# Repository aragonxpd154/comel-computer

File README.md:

<p align="center">
  <b>Um Commodore 64 de verdade — BASIC V2, tela de 7" VGA, 2 portas USB para teclado e joystick — ligado à rede por uma TSDA 4011R1.</b><br>
  Uma placa única em KiCad (esquemático, PCB roteada, arquivos de fábrica, 3D com componentes reais),<br>
  a engenharia reversa da TSDA e uma carcaça compacta com a tela inclinada, pronta para cortar a laser.
</p>

<p align="center">
  
</p>

---

## Sumário

- [Visão geral](#visão-geral)
- [Arquitetura](#arquitetura)
- [Placa COMEL](#placa-comel--o-commodore-e-a-energia-numa-placa-só)
- [Carcaça cortada a laser](#carcaça-cortada-a-laser)
- [TSDA 4011R1 — a placa de rede](#tsda-4011r1--a-placa-de-rede)
- [Lista de materiais](#lista-de-materiais)
- [Guia passo a passo](#guia-passo-a-passo)
- [Estrutura do repositório](#estrutura-do-repositório)
- [Limitações e pontos a confirmar](#limitações-e-pontos-a-confirmar)
- [Referências](#referências) · [Licença](#licença)

---

## Visão geral

A **TSDA 4011R1** é a placa de comunicação da remota FLEX TSDA usada na transmissão: um Digi Connect ME que coloca uma
porta serial na rede. Este projeto aproveita essa placa como "modem" de um **Commodore 64 recriado num Raspberry Pi
Pico 2**: o Pico emula o C64 (6502, VIC-II, SID, KERNAL e BASIC V2), mostra a imagem numa tela de 7" VGA e fala com a
TSDA pela serial. Um Telnet no IP da TSDA conversa com o programa BASIC, como uma BBS dos anos 80.

| | Conteúdo | Onde |
|---|---|---|
| 🟦 | **Placa COMEL** — Pico 2, VGA RGB332, 2 × USB host (teclado), microSD, áudio (SID), joystick, serial até a TSDA **e** a entrada da Mean Well RD-35A (5 V / 12 V) com TVS, polyfuse e LED por trilho. 132 × 64 mm, **DRC 0** | [`hardware/comel`](hardware/comel) |
| 🏭 | Gerbers X2, furação, BOM, pick-and-place, STEP, PDFs de esquemático e montagem | [`hardware/comel/fab`](hardware/comel/fab) |
| 📦 | Carcaça compacta (230 × 128 × 190 mm) com a tela de 7" inclinada 25°, chapa de 3 mm: 2 chapas de 600 × 400 mm em **SVG e DXF**, gerada a partir do layout da placa | [`case`](case) |
| 🔍 | Engenharia reversa da TSDA 4011R1, com modelo 3D reconstruído das fotos | [`docs/tsda-4011r1.md`](docs/tsda-4011r1.md) |
| 🧊 | Modelos 3D (STEP/GLB/STL) e visualizador three.js com a montagem completa | [`docs/3d`](docs/3d) |
| 💾 | **Firmware do C64** pronto para gravar ([`comel.uf2`](firmware/bin/comel.uf2)): 6510/VIC-II/CIAs/SID, VGA 640×480 em PIO, 2 × USB host para teclado, áudio PWM, LOAD/SAVE no microSD | [`firmware`](firmware) |
| 🔁 | Pipeline reprodutível: um arquivo Python descreve os circuitos; o resto é gerado | [`tools/eda/designs.py`](tools/eda/designs.py) |

---

## Arquitetura

```mermaid
flowchart LR
  AC["Tomada<br/>módulo IEC + fusível"] --> PSU["Mean Well RD-35A<br/>5 V / 4 A · 12 V / 1 A"]
  PSU -- "J10" --> PWR
  PWR -- "5 V · J11" --> TSDA
  PWR -- "12 V · J12" --> LCD
  subgraph COMEL["Placa COMEL"]
    direction TB
    PWR["Entrada da fonte<br/>TVS · polyfuse · LEDs"]
    PICO(("Pico 2<br/>emulador C64"))
    VGA["DAC RGB332"]
    KB["2 × USB-A<br/>host em PIO"]
    SD["microSD"]
    AUD["Áudio SID<br/>RC 2 polos"]
    JOY["Joystick DB9"]
    SER["Serial<br/>TTL / MAX3232"]
    PWR -- "5 V" --> PICO
  end
  PICO --> VGA -- "IDC 2×5" --> LCD["Tela de 7 pol. 800×480<br/>PCB800099"]
  KB --- PICO
  SD --- PICO
  PICO --> AUD
  JOY --> PICO
  PICO --- SER -- "UART" --> TSDA["TSDA 4011R1<br/>Digi Connect ME"]
  TSDA -- "Ethernet<br/>Telnet / HTTP" --> NET(("Rede"))
```

---

## Placa COMEL — o Commodore e a energia numa placa só

<table>
<tr>
<td width="50%"></td>
<td width="50%"></td>
</tr>
<tr><td align="center"><sub>Face superior, renderizada a partir dos Gerbers</sub></td><td align="center"><sub>Modelo 3D com os modelos STEP dos componentes</sub></td></tr>
</table>

<p align="center"><sub>Esquemático em blocos funcionais (folha A2) — <a href="docs/images/comel-schematic.svg">SVG vetorial</a> · <a href="hardware/comel/fab/comel-schematic.pdf">PDF</a></sub></p>

A revisão anterior tinha duas placas (MAIN e PWR). Agora tudo cabe em **132 × 64 mm**: o lado esquerdo é o Commodore,
o lado direito é a entrada da fonte. Só a Mean Well RD-35A fica fora da placa.

| Bloco | Componentes | Como funciona |
|---|---|---|
| Processador | U1 Pico 2 em 2 barras fêmea | RP2350 roda o emulador do C64; o USB sai pela lateral da carcaça para gravar o firmware |
| Vídeo | R1–R10, J1 | DAC de resistores RGB332 (256 cores): R/G 499 Ω · 1 kΩ · 2 kΩ, B 390 Ω · 820 Ω → 0,7 V em 75 Ω. Sincronismos com 100 Ω. Cabo flat 2×5 até a entrada J4 da controladora da tela |
| Teclado USB | J2, R11–R14, U3, F1, C17 | **USB-A duplo empilhado na borda traseira**, host full/low speed pelo PIO (Pico-PIO-USB): USB 1 em GP4/GP5, USB 2 em GP2/GP3. 27 Ω em série nas linhas de dados, USBLC6-4SC6 contra ESD, polyfuse de 1 A e 47 µF no VBUS. O USB do próprio Pico continua livre para gravar o firmware |
| Cartão | J5, R15–R19, C6 | microSD em SPI0 com pull-ups de 10 kΩ; o cartão entra pela lateral esquerda da carcaça |
| Áudio | R20–R22, C7–C9, J6 | PWM do GP20 → filtro RC de 2 polos (≈ 16 kHz) → 10 µF → jack P2. **A boca do P2 fica na borda traseira**, alinhada ao furo do painel |
| Joystick | R23–R27, J7 | DB9 macho no padrão Atari/C64; as chaves fecham para o GND, pull-ups internos, 1 kΩ de proteção |
| Serial até a TSDA | J3, JP1 · U2, C1–C5, J4 | Só TX/RX, sem controle de fluxo. TTL 3,3 V direto (de fábrica) ou RS-232 pelo MAX3232, escolhido no jumper de solda. U2/C1–C5/J4 só são montados se o CN3 da TSDA for RS-232 |
| Pico · reset | D1, C10–C12, R28, D2, SW1 | +5 V da placa → SS34 → VSYS (o USB do Pico continua isolado). SW1 é o reset |
| Entrada da fonte | J10 | Borne de 4 vias na **borda da frente, com a entrada dos fios para fora**: 1 +5 V · 2 COM · 3 +12 V · 4 COM |
| Trilho 5 V | F2 2 A, D3 SMBJ5.0CA, C13 220 µF, C14, R29/D5 verde, R31 | Polyfuse que rearma sozinho, TVS contra surto, LED de 5 V e o resistor de 330 Ω do LED da frente |
| Trilho 12 V | F3 1 A, D4 SMBJ12CA, C15 100 µF, C16, R30/D6 amarelo | Só a tela de 7" usa o 12 V |
| Saídas de energia | J11–J14 | JST-XH 2 na borda traseira: TSDA 5 V · TELA 12 V · AUX 5 V · LED da frente |

Os dois consumos (≈ 0,5 A no 5 V e ≈ 0,5 A no 12 V) ficam acima da carga mínima da RD-35A (0,3 A e 0,2 A) e com folga grande.

### Mapa de pinos do Pico 2

| GPIO | Função | GPIO | Função |
|---|---|---|---|
| GP0 / GP1 | UART0 TX / RX → TSDA | GP16–GP19 | microSD (MISO, CS, SCK, MOSI) |
| GP2 / GP3 | USB 2 D+ / D− | GP20 | áudio PWM (SID) |
| GP4 / GP5 | USB 1 D+ / D− | GP21 / GP22 | joystick cima / baixo |
| GP6–GP13 | VGA B0 B1 G0 G1 G2 R0 R1 R2 | GP26 / GP27 / GP28 | joystick esquerda / direita / tiro |
| GP14 / GP15 | VGA HSYNC / VSYNC | VSYS · 3V3 | 5 V pelo SS34 · 3,3 V do Pico |

O mesmo mapa está em [`firmware/pinagem.h`](firmware/pinagem.h).

### Conectores

| Ref. | Conector | Pinagem |
|---|---|---|
| J1 | IDC 2×5 "VGA → TELA" | 1 R · 3 G · 5 B · 7 HSYNC · 8 VSYNC · 2/4/6/9 GND · 10 NC |
| J2 | USB-A duplo empilhado (Würth 61400826021) | porta de baixo = USB 1 · porta de cima = USB 2 · 5 V até 1 A no total |
| J3 | JST-XH 3 "TSDA TTL" | 1 TX · 2 RX · 3 GND (lado do Pico) |
| J4 | JST-XH 3 "TSDA RS-232" | 1 TX · 2 RX · 3 GND (níveis RS-232, com U2) |
| J6 | P2 3,5 mm | ponta e anel = áudio, corpo = GND |
| J7 | DB9 macho | 1 cima · 2 baixo · 3 esquerda · 4 direita · 6 tiro · 8 GND |
| J10 | Borne 5,08 mm, 4 vias | 1 +5 V · 2 COM · 3 +12 V · 4 COM (da RD-35A) |
| J11 · J12 · J13 · J14 | JST-XH 2 | 1 tensão · 2 GND — TSDA 5 V · tela 12 V · auxiliar 5 V · LED da frente (já com 330 Ω) |

| Característica | Valor |
|---|---|
| Dimensões | 132 × 64 mm, cantos com raio de 2,5 mm, 4 furos M3 aterrados |
| Camadas | 2 · FR-4 1,6 mm · cobre 1 oz · ENIG |
| Montagem | SMD só na face superior (0805 / 1206 / 1812 / SOT-23 / SOT-23-6 / SMA / SMB / SOIC-16), THT nos conectores |
| Regras | trilha/isolação 0,25 / 0,2 mm · via 0,6 / 0,3 mm · borda 0,4 mm |
| Classes | `Power` 0,8 mm — GND, +5V, +5V_IN, +12V, +12V_IN, VSYS, +3V3 · `Medium` 0,5 mm — VBUS das USB |
| Roteamento | Freerouting + planos de GND nas duas faces com alívio térmico |
| Verificação | DRC 0 violações · 0 conexões pendentes · netlist = `designs.py` (68 redes / 241 conexões) |

---

## Carcaça cortada a laser

| Chapa 1 — base, traseiro, tampa, painel da tela, frente | Chapa 2 — laterais, molduras da tela |
|:---:|:---:|
|  |  |

- **Caixa:** 230 × 128 × 190 mm em chapa de **3 mm** (MDF ou acrílico) — cerca de 37% menos volume que a revisão anterior.
- **Perfil de terminal:** frente baixa (18 mm) com o LED, **tela de 7" num painel inclinado 25° para trás**, tampa reta.
  As laterais têm o perfil da caixa e recebem os dentes de todos os painéis, então toda junta é a 90°.
- **Tela:** janela de 156 × 88 mm, presa por um sanduíche de 3 molduras e 4 parafusos M3; a controladora fica atrás da trava.
- **Traseiro (gravado):** tomada IEC com chave e fusível, RS-232 e rede da TSDA, joystick, áudio e as 2 USB do teclado.
- **Lateral esquerda:** USB do Pico e microSD. **Lateral direita e tampa:** ventilação sobre a fonte.
- **Base:** furação da COMEL, da TSDA e da fonte, com o nome de cada uma gravado no lugar; ventilação embaixo da tela.

A furação da placa e a posição dos conectores são lidas de [`tools/eda/pcb_layouts.py`](tools/eda/pcb_layouts.py):
mudou a placa, rode `make case` e os cortes acompanham. Detalhes, ferragens e ordem de montagem em
[`case/README.md`](case/README.md).

```bash
make case              # medidas nominais
make case KERF=0.15    # compensa a largura do corte do seu laser
```

---

## TSDA 4011R1 — a placa de rede

| Foto | Reconstrução 3D |
|:---:|:---:|
|  | Abrir [`docs/3d/tsda-4011r1.html`](docs/3d/tsda-4011r1.html) |

Digi Connect ME (Ethernet ⇄ serial TTL) → MAX3243C (TTL ⇄ RS-232) → DB9 e header CN3, com regulador TPS7333 no verso
e um relé Axicom P2 de contato seco. Análise completa, pinagem do DB9 e o que falta medir em
[`docs/tsda-4011r1.md`](docs/tsda-4011r1.md).

---

## Lista de materiais

| Placa | Posições | Linhas de compra | Arquivos |
|---|:---:|:---:|---|
| COMEL | 85 | 46 | [BOM](hardware/comel/fab/comel-bom.csv) · [por referência](hardware/comel/fab/comel-parts.csv) · [pick-and-place](hardware/comel/fab/comel-pos.csv) |

Fora das placas: Raspberry Pi Pico 2 + 2 barras fêmea 1×20 · tela de 7" 800×480 com controladora PCB800099 (entrada VGA
640×480) · Mean Well RD-35A · módulo IEC C14 com chave e fusível de 1 A · LED vermelho de
5 mm · teclado USB · joystick Atari/C64 · cabos flat 2×5 e JST-XH · ferragens da carcaça
([`case/README.md`](case/README.md)).

---

## Guia passo a passo

### 1 · Clonar e instalar

```bash
git clone https://github.com/aragonxpd154/COMEL.git
cd COMEL
make setup          # apt (KiCad 7, Java), pip, Freerouting, three.js
make help           # lista todos os alvos
```

Testado em **Ubuntu 24.04** (KiCad 7.0.11). No **Zorin OS 17** / Ubuntu 22.04, instale o KiCad 7 pelo PPA oficial antes
(`sudo add-apt-repository ppa:kicad/kicad-7.0-releases`).

### 2 · Verificar

```bash
make check
```

```text
✓ comel: 68 redes / 241 conexões idênticas ao designs.py
✓ comel.kicad_pcb: DRC 0 violações, 0 não conectados
```

### 3 · Mandar fabricar

Envie [`comel-gerbers.zip`](hardware/comel/fab/comel-gerbers.zip) para a JLCPCB, PCBWay ou similar:
2 camadas, 1,6 mm, acabamento ENIG ou HASL, máscara da cor que quiser (o 3D usa verde).

### 4 · Montar

1. SMD primeiro (pule U2 e C1–C5 se a TSDA for TTL), depois eletrolíticos, microSD, jack, JSTs, IDC, DB9, botão,
   borne J10 e as barras fêmea do Pico. Confira que JP1 está fechado em 1-2.
2. **Sem o Pico encaixado**, ligue a RD-35A no J10: LEDs verde e amarelo acesos, +5 V em TP1 e +12 V em TP7.
3. Encaixe o Pico e confira 3,3 V em TP2.
4. Monte a carcaça ([`case/README.md`](case/README.md)) e faça os cabos.

### 5 · Gravar o firmware

1. Segure o **BOOTSEL** do Pico 2 e ligue o USB dele no computador.
2. Copie [`firmware/bin/comel.uf2`](firmware/bin/comel.uf2) para o disco `RP2350` que aparece.
3. No microSD (FAT32), crie a pasta `/c64` e ponha os `.prg`. Se tiver as ROMs originais, ponha também
   `basic.bin`, `kernal.bin` e `chargen.bin`; sem elas o C64 liga com as Open ROMs.
4. Ligue: o C64 sobe na tela de 7". Teclado em qualquer uma das 2 portas USB; F9 lista o cartão, F12 reinicia.

Para recompilar: `make firmware`. Para testar o emulador no PC sem a placa: `make fwtest`.
Detalhes e teclas em [`firmware/README.md`](firmware/README.md).

### 6 · Mexer no projeto

Tudo sai de [`tools/eda/designs.py`](tools/eda/designs.py) (circuito) e
[`tools/eda/pcb_layouts.py`](tools/eda/pcb_layouts.py) (posições):

```bash
make sch      # esquemáticos + verificação do netlist
make pcb      # posiciona, roteia e roda o DRC
make fab      # Gerbers, BOM, STEP, PDFs
make render   # texturas, 3D, imagens, carcaça e visualizador
```

---

## Estrutura do repositório

```text
COMEL/
├── hardware/
│   ├── lib/                      símbolo, footprint e modelo 3D do Pico 2 (gerados)
│   └── comel/                    projeto KiCad + fab/ (Gerbers, BOM, STEP, PDFs)
├── case/                         gerador da carcaça + saida/ (SVG, DXF, peças, carcaca.json)
├── docs/
│   ├── 3d/                       viewer.html, GLB/STL das placas, TSDA reconstruída
│   ├── images/                   renders, esquemáticos, chapas, fotos originais
│   └── tsda-4011r1.md            engenharia reversa da TSDA
├── firmware/                     firmware do C64 (C/C++, pico-sdk) + bin/comel.uf2 + teste no PC
├── tools/
│   ├── eda/                      designs.py → esquemático, PCB, fab, verificação
│   ├── render/                   texturas, STEP → GLB/STL, visualizador
│   └── build_all.py              pipeline completo
├── index.html                    redireciona o GitHub Pages para o visualizador
├── Makefile · requirements.txt · scripts/setup-ubuntu.sh
└── publicar-no-github.sh
```

---

## Limitações e pontos a confirmar

- **CN3 e CN2 da TSDA não foram medidos.** Por isso a ligação com a TSDA é feita por cabos JST (J3/J4 de sinal e J11 de
  5 V), montados conforme a pinagem medida. Se o CN3 for RS-232, monte U2/C1–C5 e mude JP1 para 2-3. Configure o Digi Connect ME sem controle de fluxo.
- **Firmware:** compilado e testado no PC (boot, teclado USB, LOAD/SAVE, SID, joystick), ainda não medido na placa. A rede pela TSDA (UART0) e o drive 1541 vêm depois — ver [`firmware/README.md`](firmware/README.md).
- **Modelo 3D do Pico 2:** simplificado (o KiCad 7 não traz o Pico); a TSDA 4011R1 foi reconstruída pelas fotos.
- **Carcaça:** conferir antes de cortar o recorte do módulo IEC, os furos da RD-35A (oblongos), as medidas reais da tela
  e da controladora, e a espessura da chapa. As juntas entre painéis vizinhos em ângulo (frente/tela e tela/tampa) são
  de topo e vão coladas.
- **ROMs do C64:** as originais têm direitos autorais; a proposta é usar as Open ROMs do MEGA65 (GPLv3).

---

## Referências

- Raspberry Pi — [Pico 2 datasheet](https://datasheets.raspberrypi.com/pico/pico-2-datasheet.pdf)
- Digi — Digi Connect ME Hardware Reference
- Texas Instruments — MAX3243C, MAX3232, TPS73xx (TPS7333) datasheets
- Mean Well — RD-35 series datasheet (Case 932A)
- MEGA65 — [Open ROMs](https://github.com/MEGA65/open-roms)
- Jean-Marc Harvengt — [MCUME](https://github.com/Jean-MarcHarvengt/MCUME)
- [Freerouting](https://github.com/freerouting/freerouting) · [three.js](https://threejs.org/) · KiCad 7

## Licença

[GPL-3.0](LICENSE) — Marcos Santos ([github.com/aragonxpd154](https://github.com/aragonxpd154)).
Mesmo fluxo de projeto do [PFC-circuit](https://github.com/aragonxpd154/PFC-circuit).

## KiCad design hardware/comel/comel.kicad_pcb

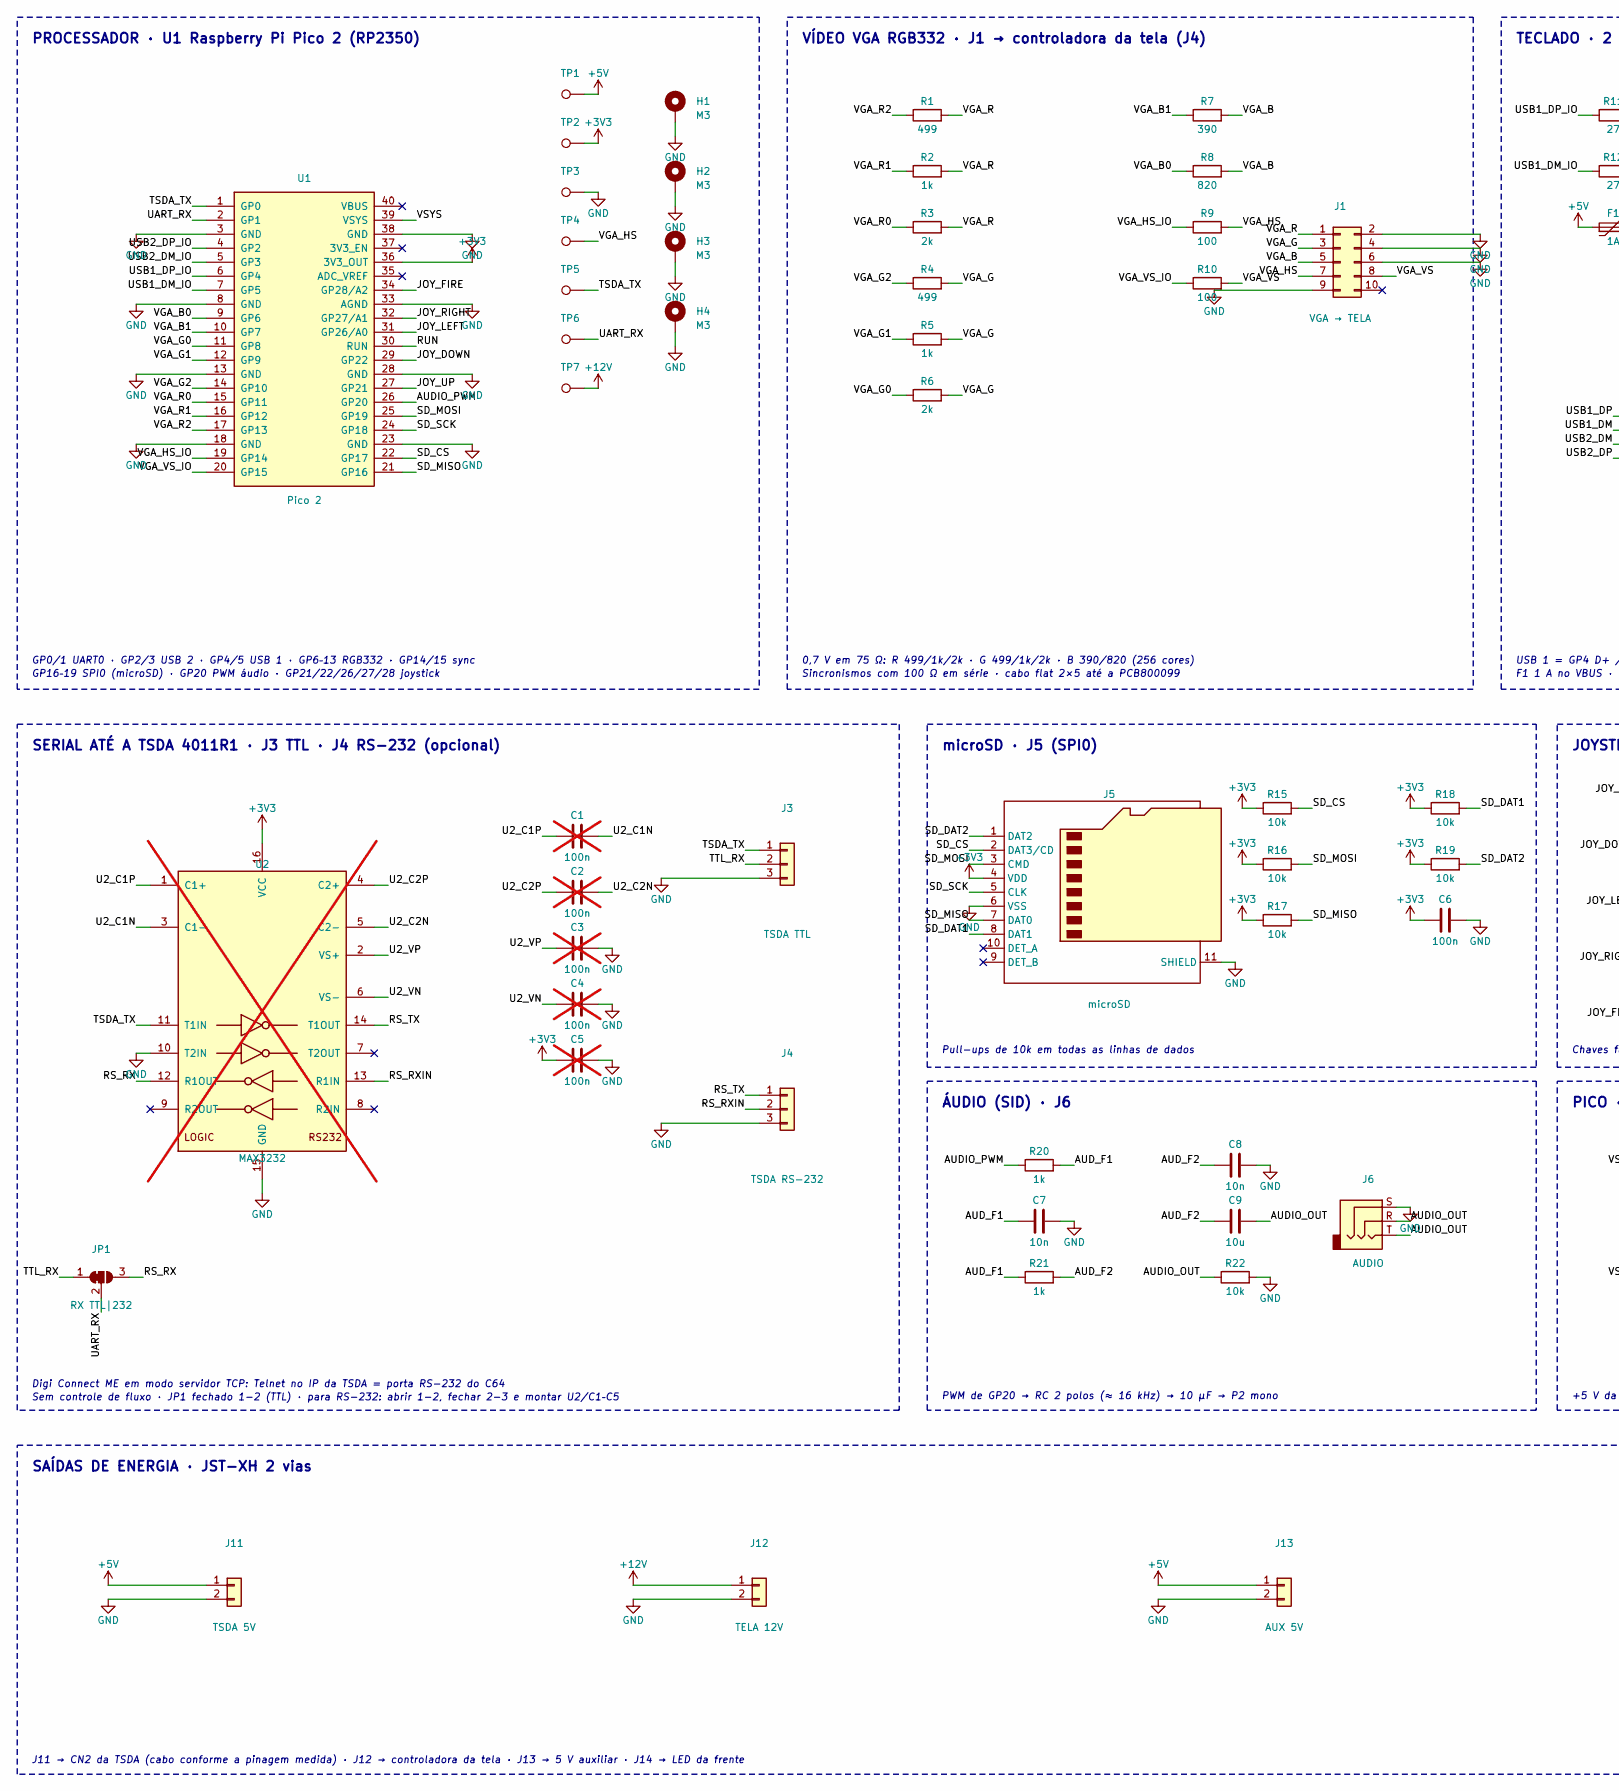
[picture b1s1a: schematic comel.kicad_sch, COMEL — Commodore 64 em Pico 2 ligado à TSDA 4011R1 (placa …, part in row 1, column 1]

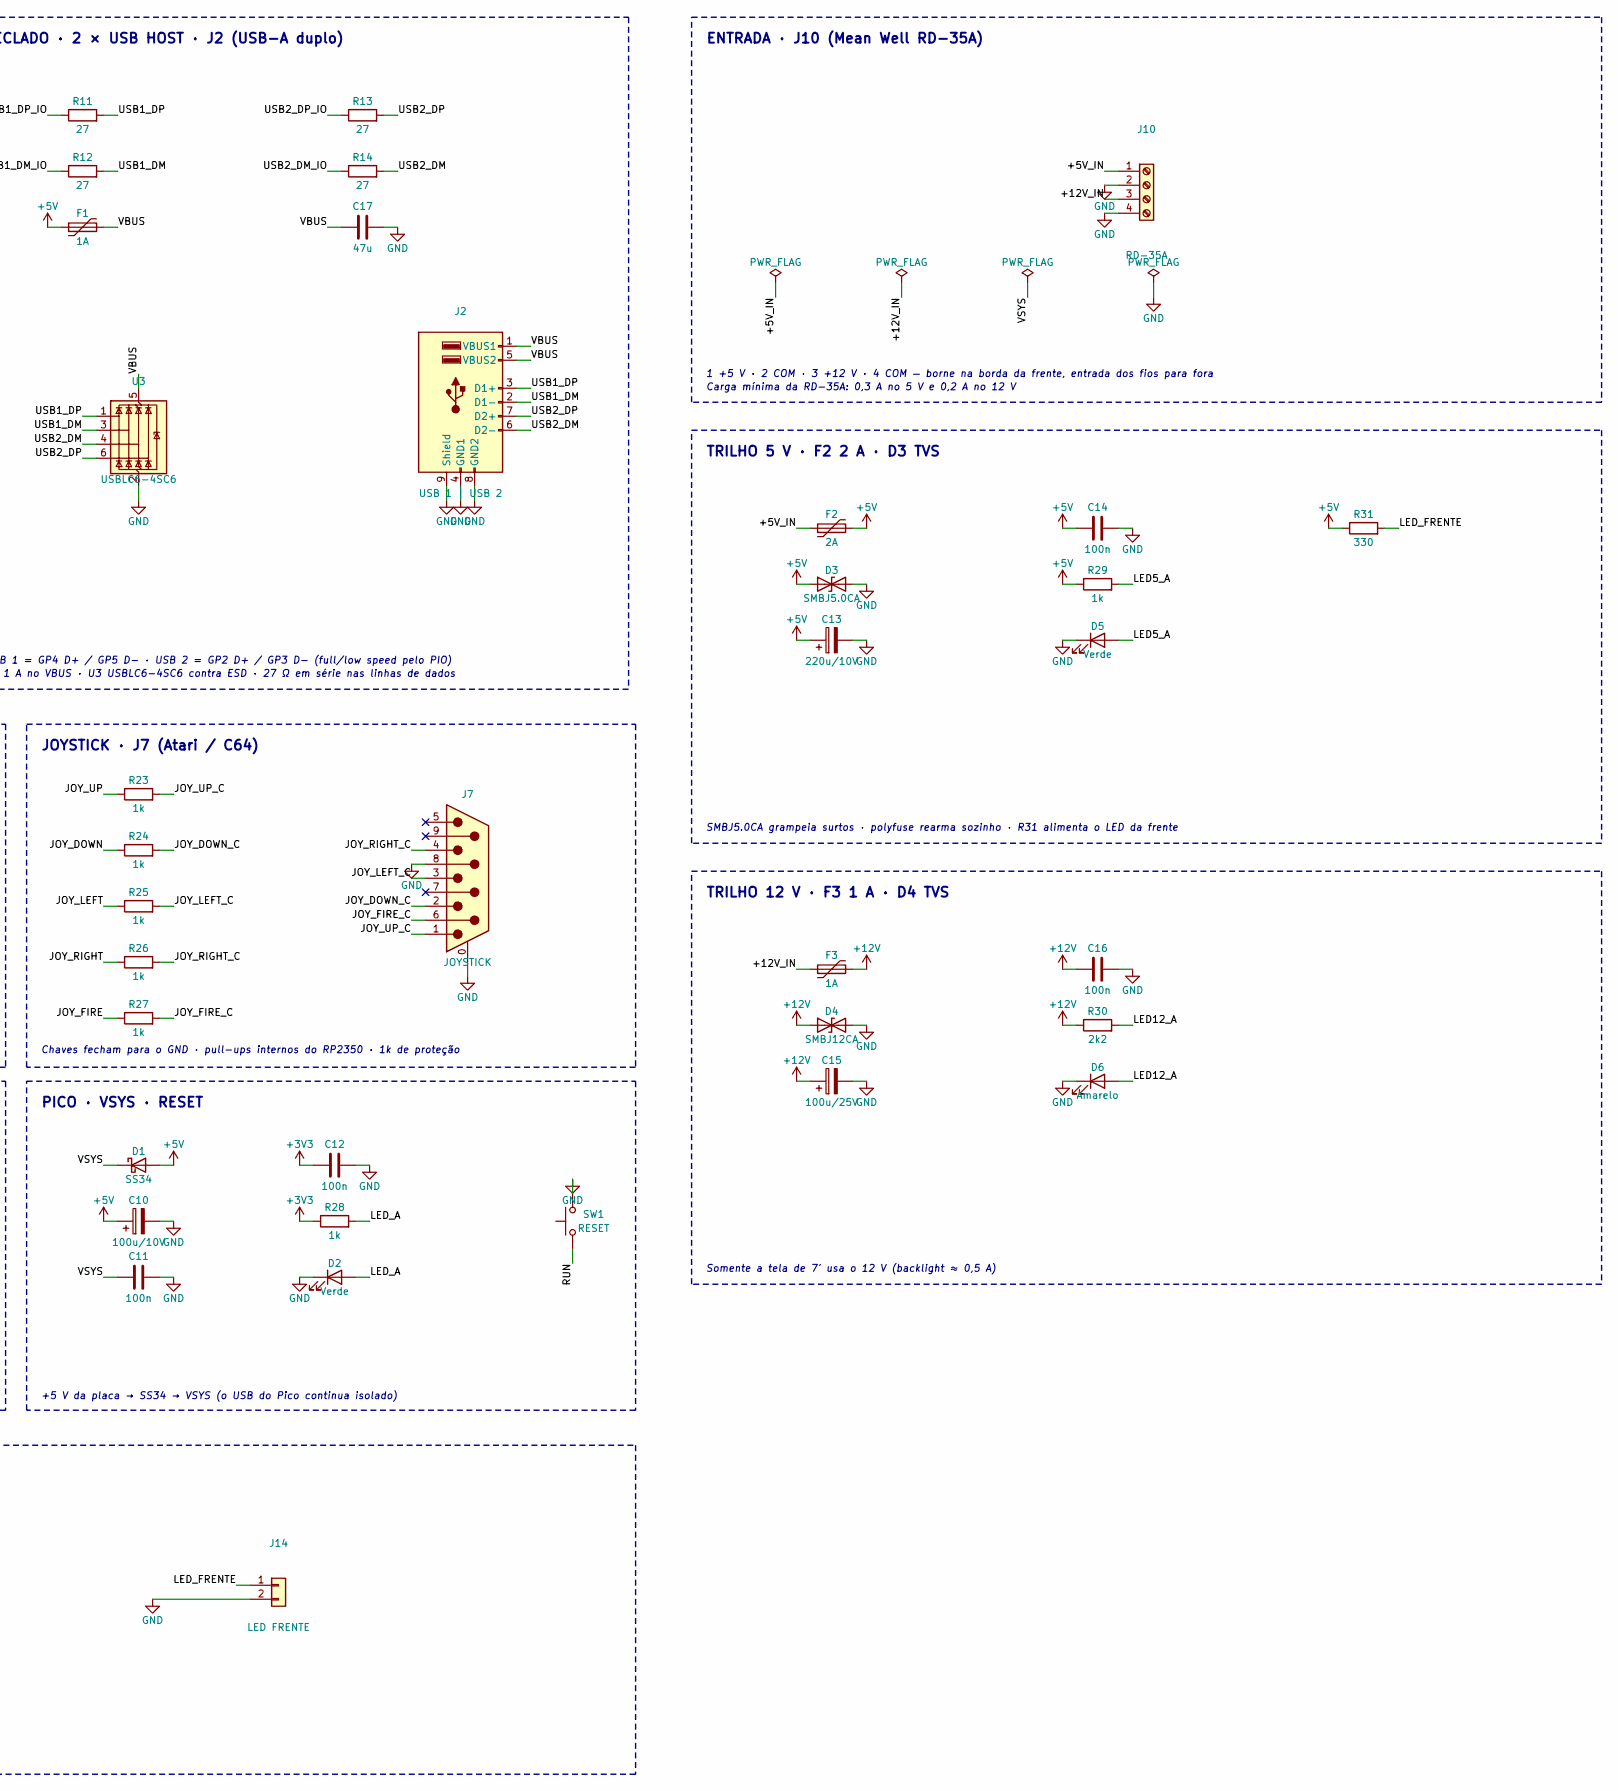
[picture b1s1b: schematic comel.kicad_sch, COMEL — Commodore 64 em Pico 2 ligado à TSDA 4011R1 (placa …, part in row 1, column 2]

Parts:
C1, C2, C3, C4, C5: 100n; C_0805_2012Metric; not fitted
C6, C11, C12, C14, C16: 100n; C_0805_2012Metric
C7, C8: 10n; C_0805_2012Metric
C9: 10u; C_1206_3216Metric
C10: 100u/10V; CP_Elec_6.3x7.7
C13: 220u/10V; CP_Elec_8x10
C15: 100u/25V; CP_Elec_8x10
C17: 47u; C_1206_3216Metric
D1: SS34; D_SMA; MPN SS34
D2, D5: Verde; LED_0805_2012Metric
D3: SMBJ5.0CA; D_SMB; MPN SMBJ5.0CA
D4: SMBJ12CA; D_SMB; MPN SMBJ12CA
D6: Amarelo; LED_0805_2012Metric
F1: 1A; Fuse_1206_3216Metric; MPN 1206L110
F2: 2A; Fuse_1812_4532Metric
F3: 1A; Fuse_1812_4532Metric
H1, H2, H3, H4: M3; MountingHole_3.2mm_M3_Pad_Via
J1: VGA → TELA; IDC-Header_2x05_P2.54mm_Vertical
J2: USB 1 | USB 2; USB_A_Wuerth_61400826021_Horizontal_Stacked; MPN 61400826021
J3: TSDA TTL; JST_XH_B3B-XH-A_1x03_P2.50mm_Vertical; MPN B3B-XH-A
J4: TSDA RS-232; JST_XH_B3B-XH-A_1x03_P2.50mm_Vertical; MPN B3B-XH-A
J5: microSD; microSD_HC_Hirose_DM3AT-SF-PEJM5; MPN DM3AT-SF-PEJM5
J6: AUDIO; Jack_3.5mm_CUI_SJ1-3523N_Horizontal; MPN SJ1-3523N
J7: JOYSTICK; DSUB-9_Male_Horizontal_P2.77x2.84mm_EdgePinOffset9.90mm_Hou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
J10: RD-35A; TerminalBlock_Phoenix_MKDS-1,5-4-5.08_1x04_P5.08mm_Horizont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
J11: TSDA 5V; JST_XH_B2B-XH-A_1x02_P2.50mm_Vertical; MPN B2B-XH-A
J12: TELA 12V; JST_XH_B2B-XH-A_1x02_P2.50mm_Vertical; MPN B2B-XH-A
J13: AUX 5V; JST_XH_B2B-XH-A_1x02_P2.50mm_Vertical; MPN B2B-XH-A
J14: LED FRENTE; JST_XH_B2B-XH-A_1x02_P2.50mm_Vertical; MPN B2B-XH-A
JP1: RX TTL|232; SolderJumper-3_P1.3mm_Bridged12_RoundedPad1.0x1.5mm
R1, R4: 499; R_0805_2012Metric
R2, R5, R20, R21, R23, R24, R25, R26, R27, R28, R29: 1k; R_0805_2012Metric
R3, R6: 2k; R_0805_2012Metric
R7: 390; R_0805_2012Metric
R8: 820; R_0805_2012Metric
R9, R10: 100; R_0805_2012Metric
R11, R12, R13, R14: 27; R_0805_2012Metric
R15, R16, R17, R18, R19, R22: 10k; R_0805_2012Metric
R30: 2k2; R_0805_2012Metric
R31: 330; R_0805_2012Metric
SW1: RESET; SW_PUSH_6mm
TP1: +5V; TestPoint_Pad_D1.5mm
TP2: +3V3; TestPoint_Pad_D1.5mm
TP3: GND; TestPoint_Pad_D1.5mm
TP4: VGA_HS; TestPoint_Pad_D1.5mm
TP5: TSDA_TX; TestPoint_Pad_D1.5mm
TP6: UART_RX; TestPoint_Pad_D1.5mm
TP7: +12V; TestPoint_Pad_D1.5mm
U1: Pico 2; RaspberryPi_Pico_Socket
U2: MAX3232; SOIC-16_3.9x9.9mm_P1.27mm; MPN MAX3232ECDR; not fitted
U3: USBLC6-4SC6; SOT-23-6; MPN USBLC6-4SC6

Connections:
+3V3: C5.1, C6.1, C12.1, J5.4 (VDD), R15.1, R16.1, R17.1, R18.1, R19.1, R28.1, TP2.1, U1.36 (3V3_OUT), U2.16 (VCC)
+5V: C10.1, C13.1, C14.1, D1.2 (A), D3.1 (A1), F1.1, F2.2, J11.1, J13.1, R29.1, R31.1, TP1.1
+5V_IN: F2.1, J10.1
+12V: C15.1, C16.1, D4.1 (A1), F3.2, J12.1, R30.1, TP7.1
+12V_IN: F3.1, J10.3
AUDIO_OUT: C9.2, J6.R, J6.T, R22.1
AUDIO_PWM: R20.1, U1.26 (GP20)
AUD_F1: C7.1, R20.2, R21.1
AUD_F2: C8.1, C9.1, R21.2
GND: C3.2, C4.2, C5.2, C6.2, C7.2, C8.2, C10.2, C11.2, C12.2, C13.2, C14.2, C15.2, C16.2, C17.2, D2.1 (K), D3.2 (A2), D4.2 (A2), D5.1 (K), D6.1 (K), H1.1, H2.1, H3.1, H4.1, J1.2, J1.4, J1.6, J1.9, J2.4 (GND1), J2.8 (GND2), J2.9 (Shield), J3.3, J4.3, J5.6 (VSS), J5.11 (SHIELD), J6.S, J7.0 (PAD), J7.8, J10.2, J10.4, J11.2, J12.2, J13.2, J14.2, R22.2, SW1.2, TP3.1, U1.3 (GND), U1.8 (GND), U1.13 (GND), U1.18 (GND), U1.23 (GND), U1.28 (GND), U1.33 (AGND), U1.38 (GND), U2.10 (T2IN), U2.15 (GND), U3.2 (GND)
JOY_DOWN: R24.1, U1.29 (GP22)
JOY_DOWN_C: J7.2, R24.2
JOY_FIRE: R27.1, U1.34 (GP28/A2)
JOY_FIRE_C: J7.6, R27.2
JOY_LEFT: R25.1, U1.31 (GP26/A0)
JOY_LEFT_C: J7.3, R25.2
JOY_RIGHT: R26.1, U1.32 (GP27/A1)
JOY_RIGHT_C: J7.4, R26.2
JOY_UP: R23.1, U1.27 (GP21)
JOY_UP_C: J7.1, R23.2
LED5_A: D5.2 (A), R29.2
LED12_A: D6.2 (A), R30.2
LED_A: D2.2 (A), R28.2
LED_FRENTE: J14.1, R31.2
RS_RX: JP1.3 (B), U2.12 (R1OUT)
RS_RXIN: J4.2, U2.13 (R1IN)
RS_TX: J4.1, U2.14 (T1OUT)
RUN: SW1.1, U1.30 (RUN)
SD_CS: J5.2 (DAT3/CD), R15.2, U1.22 (GP17)
SD_DAT1: J5.8 (DAT1), R18.2
SD_DAT2: J5.1 (DAT2), R19.2
SD_MISO: J5.7 (DAT0), R17.2, U1.21 (GP16)
SD_MOSI: J5.3 (CMD), R16.2, U1.25 (GP19)
SD_SCK: J5.5 (CLK), U1.24 (GP18)
TSDA_TX: J3.1, TP5.1, U1.1 (GP0), U2.11 (T1IN)
TTL_RX: J3.2, JP1.1 (A)
U2_C1N: C1.2, U2.3 (C1-)
U2_C1P: C1.1, U2.1 (C1+)
U2_C2N: C2.2, U2.5 (C2-)
U2_C2P: C2.1, U2.4 (C2+)
U2_VN: C4.1, U2.6 (VS-)
U2_VP: C3.1, U2.2 (VS+)
UART_RX: JP1.2 (C), TP6.1, U1.2 (GP1)
USB1_DM: J2.2 (D1-), R12.2, U3.3 (I/O2)
USB1_DM_IO: R12.1, U1.7 (GP5)
USB1_DP: J2.3 (D1+), R11.2, U3.1 (I/O1)
USB1_DP_IO: R11.1, U1.6 (GP4)
USB2_DM: J2.6 (D2-), R14.2, U3.4 (I/O3)
USB2_DM_IO: R14.1, U1.5 (GP3)
USB2_DP: J2.7 (D2+), R13.2, U3.6 (I/O4)
USB2_DP_IO: R13.1, U1.4 (GP2)
VBUS: C17.1, F1.2, J2.1 (VBUS1), J2.5 (VBUS2), U3.5 (VBUS)
VGA_B: J1.5, R7.2, R8.2
VGA_B0: R8.1, U1.9 (GP6)
VGA_B1: R7.1, U1.10 (GP7)
VGA_G: J1.3, R4.2, R5.2, R6.2
VGA_G0: R6.1, U1.11 (GP8)
VGA_G1: R5.1, U1.12 (GP9)
VGA_G2: R4.1, U1.14 (GP10)
VGA_HS: J1.7, R9.2, TP4.1
VGA_HS_IO: R9.1, U1.19 (GP14)
VGA_R: J1.1, R1.2, R2.2, R3.2
VGA_R0: R3.1, U1.15 (GP11)
VGA_R1: R2.1, U1.16 (GP12)
VGA_R2: R1.1, U1.17 (GP13)
VGA_VS: J1.8, R10.2
VGA_VS_IO: R10.1, U1.20 (GP15)
VSYS: C11.1, D1.1 (K), U1.39 (VSYS)

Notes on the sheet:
PROCESSADOR · U1 Raspberry Pi Pico 2 (RP2350)
GP0/1 UART0 · GP2/3 USB 2 · GP4/5 USB 1 · GP6–13 RGB332 · GP14/15 sync
GP16–19 SPI0 (microSD) · GP20 PWM áudio · GP21/22/26/27/28 joystick
VÍDEO VGA RGB332 · J1 → controladora da tela (J4)
0,7 V em 75 Ω: R 499/1k/2k · G 499/1k/2k · B 390/820 (256 cores)
Sincronismos com 100 Ω em série · cabo flat 2×5 até a PCB800099
TECLADO · 2 × USB HOST · J2 (USB-A duplo)
USB 1 = GP4 D+ / GP5 D− · USB 2 = GP2 D+ / GP3 D− (full/low speed pelo PIO)
F1 1 A no VBUS · U3 USBLC6-4SC6 contra ESD · 27 Ω em série nas linhas de dados
SERIAL ATÉ A TSDA 4011R1 · J3 TTL · J4 RS-232 (opcional)
Digi Connect ME em modo servidor TCP: Telnet no IP da TSDA = porta RS-232 do C64
Sem controle de fluxo · JP1 fechado 1-2 (TTL) · para RS-232: abrir 1-2, fechar 2-3 e montar U2/C1–C5
microSD · J5 (SPI0)
Pull-ups de 10k em todas as linhas de dados
ÁUDIO (SID) · J6
PWM de GP20 → RC 2 polos (≈ 16 kHz) → 10 µF → P2 mono
JOYSTICK · J7 (Atari / C64)
Chaves fecham para o GND · pull-ups internos do RP2350 · 1k de proteção
PICO · VSYS · RESET
+5 V da placa → SS34 → VSYS (o USB do Pico continua isolado)
ENTRADA · J10 (Mean Well RD-35A)
1 +5 V · 2 COM · 3 +12 V · 4 COM — borne na borda da frente, entrada dos fios para fora
Carga mínima da RD-35A: 0,3 A no 5 V e 0,2 A no 12 V
TRILHO 5 V · F2 2 A · D3 TVS
SMBJ5.0CA grampeia surtos · polyfuse rearma sozinho · R31 alimenta o LED da frente
TRILHO 12 V · F3 1 A · D4 TVS
Somente a tela de 7' usa o 12 V (backlight ≈ 0,5 A)
SAÍDAS DE ENERGIA · JST-XH 2 vias
J11 → CN2 da TSDA (cabo conforme a pinagem medida) · J12 → controladora da tela · J13 → 5 V auxiliar · J14 → LED da frente

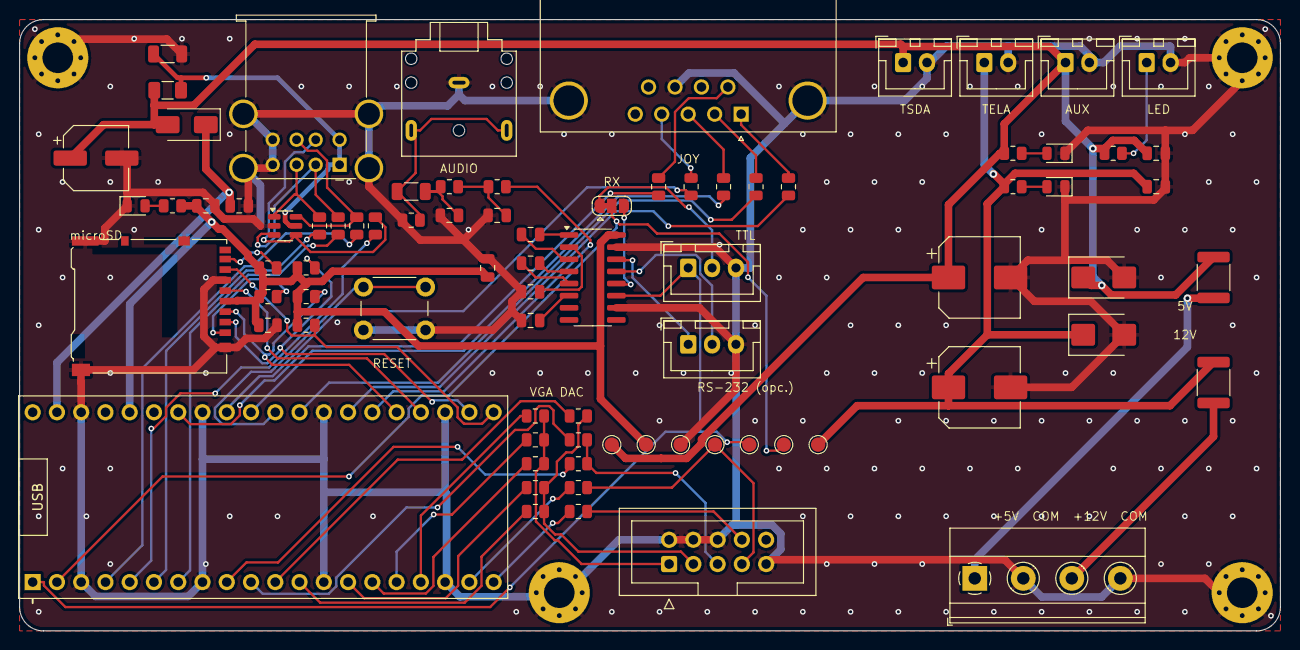
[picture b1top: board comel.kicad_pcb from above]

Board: 2 copper layers, 132.0 x 64.0 mm, 85 parts (0 on the bottom side), 68 nets.

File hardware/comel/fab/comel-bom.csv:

Item,Qtd,Referências,Valor,Footprint,Descrição,MPN,Nota
1,1,U1,Pico 2,RaspberryPi_Pico_Socket,"Raspberry Pi Pico 2 (RP2350) + 2 barras fêmea 1×20 de 2,54 mm — emulador C64",,
2,1,U2,MAX3232,SOIC-16_3.9x9.9mm_P1.27mm,"Transceptor RS-232 3,3 V — só monte se o CN3 da TSDA for RS-232",MAX3232ECDR,NÃO MONTAR (opcional) / opcional
3,1,U3,USBLC6-4SC6,SOT-23-6,Proteção ESD das 4 linhas de dados das duas portas USB,USBLC6-4SC6,
4,1,D1,SS34,D_SMA,Schottky 3 A 40 V — 5 V → VSYS (isola o USB do Pico),SS34,
5,1,D4,SMBJ12CA,D_SMB,TVS 12 V bidirecional 600 W — surtos no 12 V,SMBJ12CA,
6,1,D3,SMBJ5.0CA,D_SMB,TVS 5 V bidirecional 600 W — surtos no 5 V,SMBJ5.0CA,
7,1,D6,Amarelo,LED_0805_2012Metric,LED do trilho de 12 V,,
8,1,D2,Verde,LED_0805_2012Metric,"LED indicador de 3,3 V",,
9,1,D5,Verde,LED_0805_2012Metric,LED do trilho de 5 V,,
10,1,F1,1A,Fuse_1206_3216Metric,Polyfuse 1206 1 A — VBUS das duas portas USB,1206L110,
11,1,F3,1A,Fuse_1812_4532Metric,Polyfuse 1812 1 A — trilho de 12 V,,
12,1,F2,2A,Fuse_1812_4532Metric,Polyfuse 1812 2 A — trilho de 5 V,,
13,2,R9 R10,100,R_0805_2012Metric,Resistor SMD 0805 1 %,,
14,6,R15 R16 R17 R18 R19 R22,10k,R_0805_2012Metric,Resistor SMD 0805 1 %,,
15,11,R2 R5 R20 R21 R23 R24 R25 R26 R27 R28 R29,1k,R_0805_2012Metric,Resistor SMD 0805 1 %,,
16,4,R11 R12 R13 R14,27,R_0805_2012Metric,Resistor SMD 0805 1 %,,
17,2,R3 R6,2k,R_0805_2012Metric,Resistor SMD 0805 1 %,,
18,1,R30,2k2,R_0805_2012Metric,Resistor SMD 0805 1 %,,
19,1,R31,330,R_0805_2012Metric,Resistor SMD 0805 1 %,,
20,1,R7,390,R_0805_2012Metric,Resistor SMD 0805 1 %,,
21,2,R1 R4,499,R_0805_2012Metric,Resistor SMD 0805 1 %,,
22,1,R8,820,R_0805_2012Metric,Resistor SMD 0805 1 %,,
23,5,C1 C2 C3 C4 C5,100n,C_0805_2012Metric,Capacitor cerâmico SMD 0805 X7R,,NÃO MONTAR (opcional) / opcional
24,5,C6 C11 C12 C14 C16,100n,C_0805_2012Metric,Capacitor cerâmico SMD 0805 X7R,,
25,2,C7 C8,10n,C_0805_2012Metric,Capacitor cerâmico SMD 0805 X7R,,
26,1,C9,10u,C_1206_3216Metric,Capacitor cerâmico SMD 1206 X5R 16 V,,
27,1,C17,47u,C_1206_3216Metric,Capacitor cerâmico SMD 1206 X5R 16 V,,
28,1,C10,100u/10V,CP_Elec_6.3x7.7,Capacitor eletrolítico SMD 6.3x7.7 mm,,
29,1,C15,100u/25V,CP_Elec_8x10,Capacitor eletrolítico SMD 8x10 mm,,
30,1,C13,220u/10V,CP_Elec_8x10,Capacitor eletrolítico SMD 8x10 mm,,
31,1,J7,JOYSTICK,DSUB-9_Male_Horizontal_P2.77x2.84mm_EdgePinOffset9.90mm_Housed_MountingHolesOffset11.32mm,"DB9 macho 90° — joystick Atari/C64 (1 cima, 2 baixo, 3 esq., 4 dir., 6 tiro, 8 GND)",,
32,1,J5,microSD,microSD_HC_Hirose_DM3AT-SF-PEJM5,Soquete microSD push-push — programas .PRG e imagens .D64,DM3AT-SF-PEJM5,
33,1,J10,RD-35A,"TerminalBlock_Phoenix_MKDS-1,5-4-5.08_1x04_P5.08mm_Horizontal","Borne 4 vias 5,08 mm na borda da frente — CH1 (+5 V) e CH2 (+12 V) da RD-35A",,
34,1,J2,USB 1 | USB 2,USB_A_Wuerth_61400826021_Horizontal_Stacked,"USB-A duplo empilhado, 90° — teclado USB (e mouse/joystick USB no firmware)",61400826021,
35,1,J6,AUDIO,Jack_3.5mm_CUI_SJ1-3523N_Horizontal,"Jack P2 3,5 mm — saída do SID (mono nos dois canais)",SJ1-3523N,
36,1,J13,AUX 5V,JST_XH_B2B-XH-A_1x02_P2.50mm_Vertical,"Saída 5 V auxiliar (ventoinha, fita de LED...)",B2B-XH-A,
37,1,J14,LED FRENTE,JST_XH_B2B-XH-A_1x02_P2.50mm_Vertical,LED vermelho de 5 mm do painel da frente (anodo no pino 1),B2B-XH-A,
38,1,J12,TELA 12V,JST_XH_B2B-XH-A_1x02_P2.50mm_Vertical,"Saída 12 V → controladora PCB800099 da tela de 7""",B2B-XH-A,
39,1,J11,TSDA 5V,JST_XH_B2B-XH-A_1x02_P2.50mm_Vertical,Saída 5 V → CN2 da TSDA 4011R1 (cabo conforme a pinagem medida),B2B-XH-A,
40,1,J4,TSDA RS-232,JST_XH_B3B-XH-A_1x03_P2.50mm_Vertical,JST-XH 3 vias — serial RS-232 até a TSDA (só com o U2 montado),B3B-XH-A,
41,1,J3,TSDA TTL,JST_XH_B3B-XH-A_1x03_P2.50mm_Vertical,"JST-XH 3 vias — serial TTL 3,3 V até a TSDA (TX, RX, GND), sem controle de fluxo",B3B-XH-A,
42,1,J1,VGA → TELA,IDC-Header_2x05_P2.54mm_Vertical,Cabeçalho IDC 2×5 — cabo flat até a entrada VGA (J4) da controladora PCB800099,,
43,1,JP1,RX TTL|232,SolderJumper-3_P1.3mm_Bridged12_RoundedPad1.0x1.5mm,Escolhe a origem do RX: 1-2 TTL (de fábrica) · 2-3 MAX3232,,
44,1,SW1,RESET,SW_PUSH_6mm,Botão de reset do Pico (RUN → GND),,
45,7,TP1 TP2 TP3 TP4 TP5 TP6 TP7,—,TestPoint_Pad_D1.5mm,"Ponto de teste SMD Ø1,5 mm",,
46,4,H1 H2 H3 H4,—,MountingHole_3.2mm_M3_Pad_Via,Furo de fixação M3 aterrado (espaçador de 8 mm),,

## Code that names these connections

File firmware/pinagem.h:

/*
 * COMEL — mapa de pinos da placa COMEL (Raspberry Pi Pico 2 / RP2350)
 * Gerado a partir de tools/eda/designs.py (PICO_PINS). Use no port do emulador.
 */
#pragma once

/* Serial até a TSDA 4011R1 (Digi Connect ME) — UART0 sem controle de fluxo
 * (configure o Digi Connect ME com "Flow control: None") */
#define TSDA_UART        uart0
#define PIN_TSDA_TX      0   /* GP0  → J3.1 (TTL) e MAX3232 T1IN  */
#define PIN_TSDA_RX      1   /* GP1  ← JP1 (J3.2 TTL ou MAX3232 R1OUT) */

/* 2 × USB host (teclado, mouse, joystick USB) pelo PIO — biblioteca Pico-PIO-USB.
 * D− é sempre o pino seguinte ao D+ (PIO_USB_PINOUT_DPDM). 27 Ω em série na placa. */
#define PIN_USB1_DP      4   /* GP4 → J2 porta de baixo, D+ (GP5 = D−) */
#define PIN_USB2_DP      2   /* GP2 → J2 porta de cima,  D+ (GP3 = D−) */

/* Vídeo VGA RGB332 — 8 pinos consecutivos para o PIO (B0 é o menos significativo) */
#define PIN_VGA_BASE     6   /* GP6 B0, GP7 B1, GP8 G0, GP9 G1, GP10 G2, GP11 R0, GP12 R1, GP13 R2 */
#define PIN_VGA_HSYNC    14
#define PIN_VGA_VSYNC    15

/* microSD — SPI0 */
#define SD_SPI           spi0
#define PIN_SD_MISO      16
#define PIN_SD_CS        17
#define PIN_SD_SCK       18
#define PIN_SD_MOSI      19

/* Áudio (SID) — PWM no GP20, filtro RC de 2 polos na placa */
#define PIN_AUDIO_PWM    20

/* Joystick Atari/C64 (ativo em nível baixo — ligar os pull-ups internos) */
#define PIN_JOY_UP       21
#define PIN_JOY_DOWN     22
#define PIN_JOY_LEFT     26
#define PIN_JOY_RIGHT    27
#define PIN_JOY_FIRE     28

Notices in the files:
README.md:
https://img.shields.io/badge/licen%C3%A7a-GPL--3.0-d6ac48
hardware/comel/comel.kicad_pcb:
REV 1.0 · 2026 · GPL-3.0
hardware/comel/comel.kicad_sch:
Licença GPL-3.0 · github.com/aragonxpd154/COMEL
